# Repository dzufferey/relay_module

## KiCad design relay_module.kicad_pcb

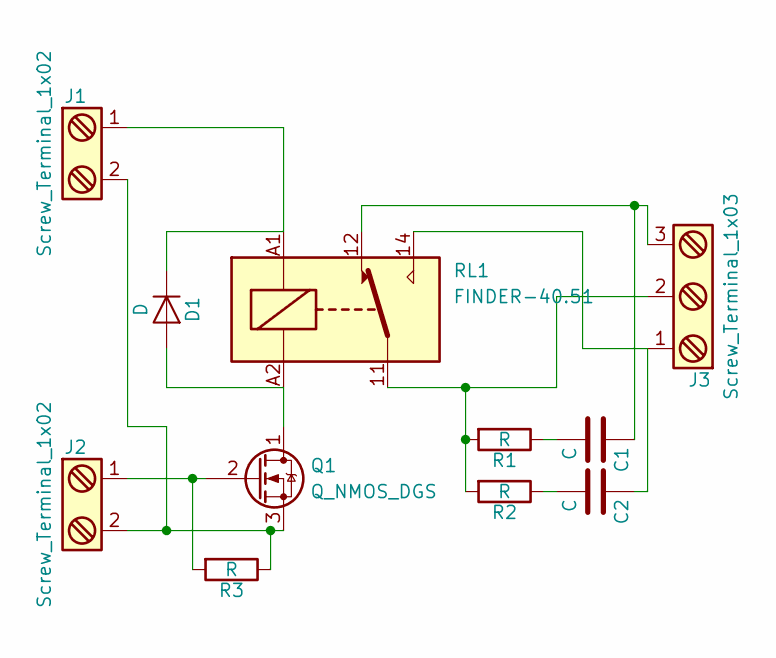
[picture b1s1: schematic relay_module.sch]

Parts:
C1, C2: C; C_Disc_D5.1mm_W3.2mm_P5.00mm
D1: D; D_DO-41_SOD81_P7.62mm_Horizontal
J1: Screw_Terminal_1x02; TerminalBlock_Pheonix_MKDS1.5-2pol
J2: Screw_Terminal_1x02; TerminalBlock_Pheonix_PT-3.5mm_2pol
J3: Screw_Terminal_1x03; TerminalBlock_Pheonix_MKDS1.5-3pol
Q1: Q_NMOS_DGS; TO-92_Molded_Wide_Reverse
R1, R2, R3: R; R_Axial_DIN0207_L6.3mm_D2.5mm_P7.62mm_Horizontal
RL1: FINDER-40.51; Relay_SPDT_Schrack-RT1_RM5mm

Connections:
unnamed: C1.1, J3.3, RL1.12
unnamed: C1.2, R1.1
unnamed: C2.1, J3.1, RL1.14
unnamed: C2.2, R2.1
unnamed: D1.1 (K), J1.1, RL1.A1
unnamed: D1.2 (A), Q1.1 (D), RL1.A2
unnamed: J1.2, J2.2, Q1.3 (S), R3.1
unnamed: J2.1, Q1.2 (G), R3.2
unnamed: J3.2, R1.2, R2.2, RL1.11

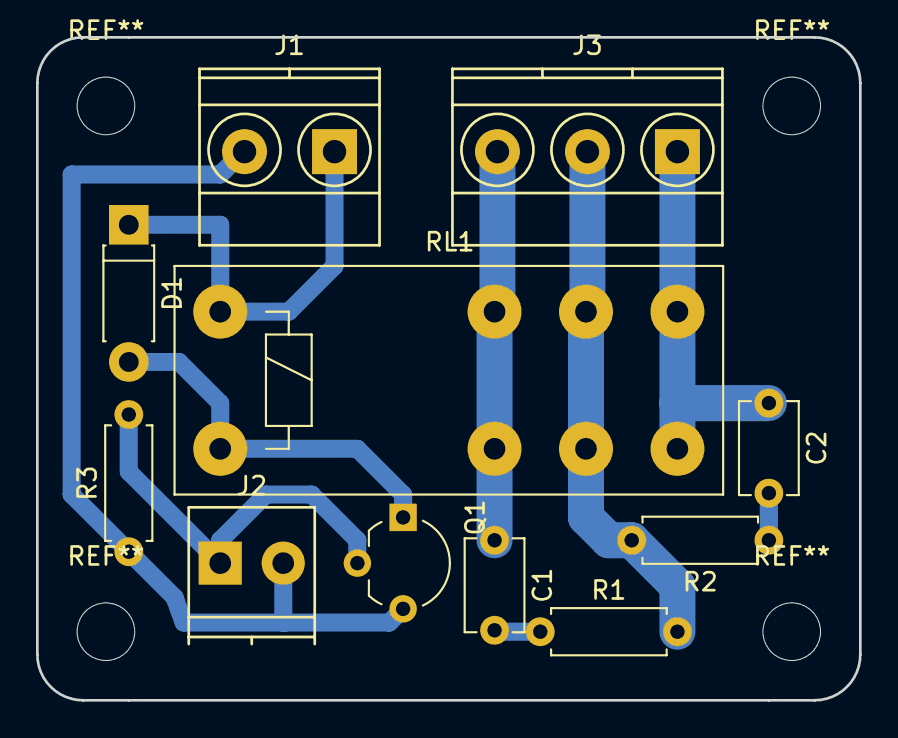
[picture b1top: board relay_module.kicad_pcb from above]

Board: 2 copper layers, 45.7 x 36.8 mm, 11 parts (0 on the bottom side), 9 nets.

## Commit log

2017-11-01 first version
2017-11-25 add pull-down resistor for transitor
